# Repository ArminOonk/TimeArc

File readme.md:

# Preparing the raspberry pi

## Update and install packages
Use the following commands to get the RPi ready

	sudo apt-get remove --purge desktop-base lightdm lxappearance lxde-common lxde-icon-theme lxinput lxpanel lxpolkit lxrandr lxsession-edit lxshortcut lxtask lxterminal
	sudo apt-get remove --purge obconf openbox raspberrypi-artwork 
	sudo apt-get remove --purge xarchiver xinit xserver-xorg 
	sudo apt-get remove --purge xserver-xorg-video-fbdev x11-utils x11-common x11-session utils
	sudo apt-get remove wolfram-*
	sudo apt-get update
	sudo apt-get upgrade
	sudo apt-get autoremove
	sudo rpi-update

# ESP Wifi
To get the esp wifi working first check the hardware. The APR2016 version has an error in the schematic. CH_PD is not connected to the correct pin.

In stall the driver using the instruction on the following website: http://oshlab.com/esp8266-raspberry-pi-gpio-wifi/

	cd ~
	git clone https://github.com/oshlab/esp8089.git
	cd esp8089
	sudo sh install
	sudo reboot
	sudo iwlist scan
	ifconfig

Check if wlan0 is visible. Now connect it to the wifi
	
	sudo nano /etc/wpa_supplicant/wpa_supplicant.conf

	network={
	ssid="testing"
	psk="testingPassword"
	}
	
Run the following commands if there is no internet connection (Test by using `ping 8.8.8.8`)

	sudo ifdown wlan0
	sudo ifup wlan0

# Install instructions

## Python packages
install pyfeed-0.7.4 and xe-0.7.4 from the Software directory

## Settings
Create a timearcPrivate.py file using the example

Add the following lines to /etc/rc.local

	sleep 30
	/home/pi/timearc/Software/startup

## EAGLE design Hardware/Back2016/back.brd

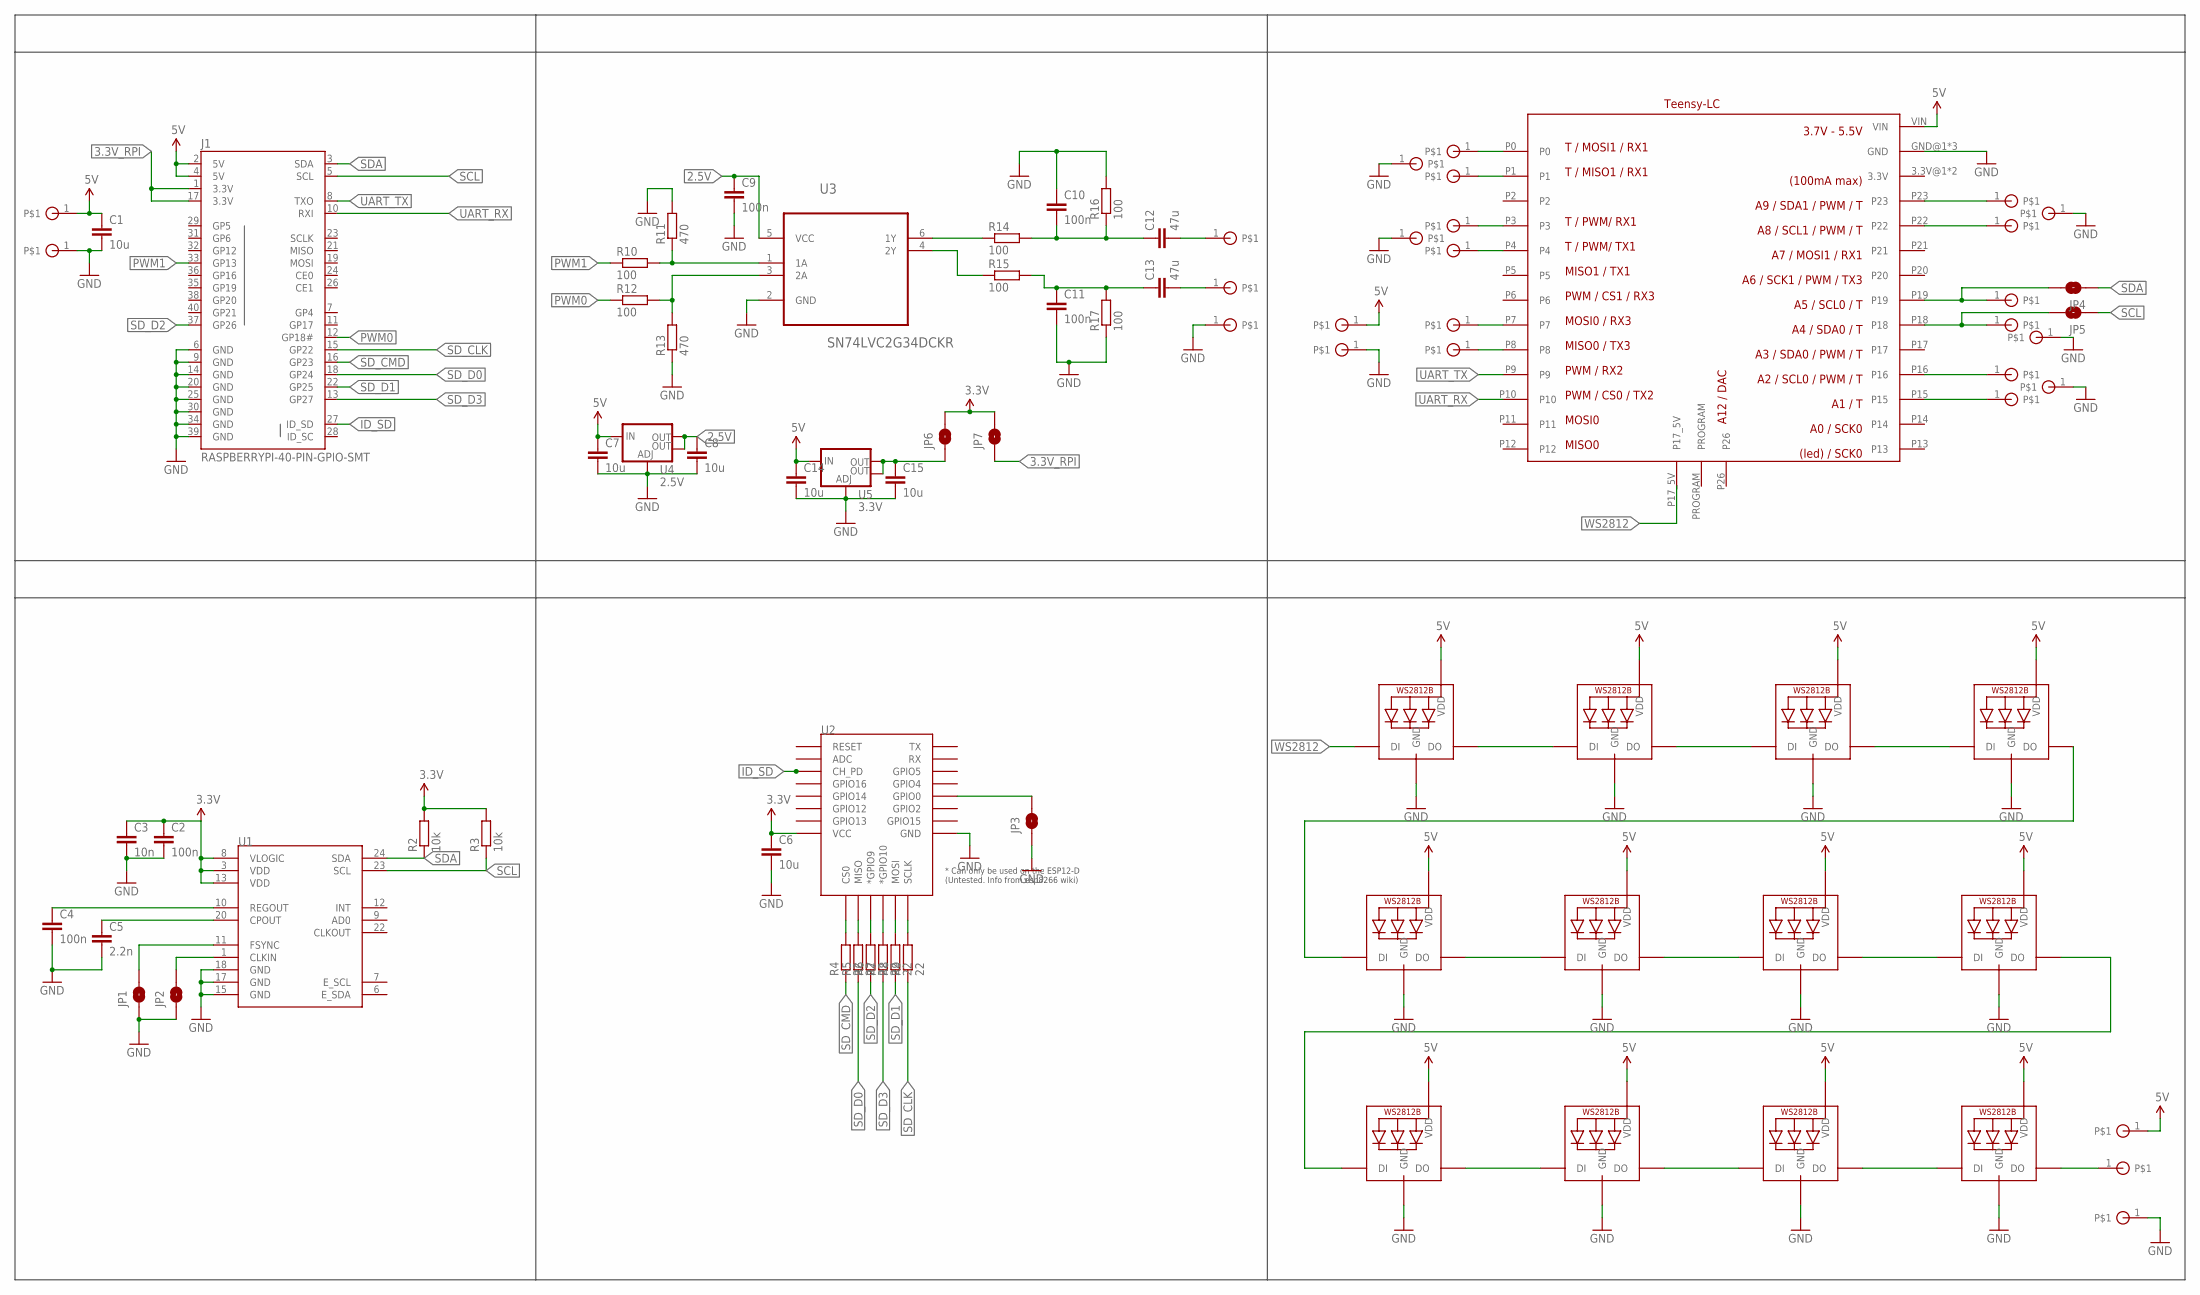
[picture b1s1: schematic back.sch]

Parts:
5V_FRONT, 5V_POWER, 5V_WS1282: SOLDER_PAD
AUDIO_GND: SOLDER_PAD
AUDIO_L: SOLDER_PAD
AUDIO_R: SOLDER_PAD
C1, C6, C7, C8, C14, C15: 10u; C0805
C2, C4, C9, C10, C11: 100n; C0603
C3: 10n; C0603
C5: 2.2n; C0603
C12, C13: 47u; C0805
DO_WS1282: SOLDER_PAD
GND_FRONT: SOLDER_PAD
GND_POWER: SOLDER_PAD
GND_T1_T2, GND_T3_T4, GND_T5_T6, GND_T7_T8: SOLDER_PAD
GND_T_SPARE: SOLDER_PAD
GND_WS2812: SOLDER_PAD
J1: RASPBERRYPI-40-PIN-GPIO-SMT; 2X20-SHROUDED-SMT
JP1, JP2, JP3, JP4, JP5, JP6, JP7: JUMPER-PAD-2-NOYES_SILK; PAD-JUMPER-2-NO_YES_SILK
LED1, LED2, LED3, LED4, LED5, LED6, LED7, LED8, LED9, LED10, LED11, LED12: WS2812B5050; WS2812B
R2, R3: 10k; R0603
R4, R5, R6, R7, R8, R9: 22; R0603
R10, R12, R14, R15, R16, R17: 100; R0603
R11, R13: 470; R0603
RX3: SOLDER_PAD
SCL/TOUCH: SOLDER_PAD
SDA/TOUCH: SOLDER_PAD
TOUCH1, TOUCH2, TOUCH3, TOUCH4, TOUCH5, TOUCH6, TOUCH7, TOUCH8: SOLDER_PAD
TX3: SOLDER_PAD
U1: MPU-9150QFN-24-NP; QFN-24-NP
U2: ESP12ESMD; ESP12E-SMD
U3: SN74LVC2G34DCKR; SOT65P210X110-6N
U4: 2.5V; SOT223
U5: 3.3V; SOT223
U$4: TEENSY_LCSMD; TEENSY_LC_SMD

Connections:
2.5V: C8.1, C9.1, U3.5 (VCC), U4.2 (OUT), U4.4 (OUT)
3.3V: C2.1, C3.1, C6.1, JP6.2, JP7.2, R2.2, R3.2, U1.3 (VDD), U1.8 (VLOGIC), U1.13 (VDD), U2.VCC
3.3V_RPI: J1.1 (3.3V), J1.17 (3.3V), JP7.1
5V: 5V_FRONT.1, 5V_POWER.1, 5V_WS1282.1, C1.1, C7.1, C14.1, J1.2 (5V), J1.4 (5V), LED1.1-VDD (VDD), LED2.1-VDD (VDD), LED3.1-VDD (VDD), LED4.1-VDD (VDD), LED5.1-VDD (VDD), LED6.1-VDD (VDD), LED7.1-VDD (VDD), LED8.1-VDD (VDD), LED9.1-VDD (VDD), LED10.1-VDD (VDD), LED11.1-VDD (VDD), LED12.1-VDD (VDD), U4.3 (IN), U5.3 (IN), U$4.VIN
GND: AUDIO_GND.1, C1.2, C2.2, C3.2, C4.2, C5.2, C6.2, C7.2, C8.2, C9.2, C10.1, C11.2, C14.2, C15.2, GND_FRONT.1, GND_POWER.1, GND_T1_T2.1, GND_T3_T4.1, GND_T5_T6.1, GND_T7_T8.1, GND_T_SPARE.1, GND_WS2812.1, J1.6 (GND), J1.9 (GND), J1.14 (GND), J1.20 (GND), J1.25 (GND), J1.30 (GND), J1.34 (GND), J1.39 (GND), JP1.1, JP2.1, JP3.1, LED1.3-GND (GND), LED2.3-GND (GND), LED3.3-GND (GND), LED4.3-GND (GND), LED5.3-GND (GND), LED6.3-GND (GND), LED7.3-GND (GND), LED8.3-GND (GND), LED9.3-GND (GND), LED10.3-GND (GND), LED11.3-GND (GND), LED12.3-GND (GND), R11.2, R13.1, R16.2, R17.1, U1.15 (GND), U1.17 (GND), U1.18 (GND), U2.GND, U3.2 (GND), U4.1 (ADJ), U5.1 (ADJ), U$4.GND@1 (GND), U$4.GND@2 (GND), U$4.GND@3 (GND)
ID_SD: J1.27 (ID_SD), U2.CH_PD
unnamed: JP2.2, U1.1 (CLKIN)
unnamed: JP1.2, U1.11 (FSYNC)
unnamed: C5.1, U1.20 (CPOUT)
unnamed: C4.1, U1.10 (REGOUT)
unnamed: R14.1, U3.6 (1Y)
unnamed: R4.2, U2.CS0
unnamed: R5.2, U2.MISO
unnamed: R6.2, U2.GPIO9 (*GPIO9)
unnamed: R7.2, U2.GPIO10 (*GPIO10)
unnamed: R8.2, U2.MOSI
unnamed: R9.2, U2.SCLK
unnamed: JP3.2, U2.GPIO0
unnamed: R10.2, R11.1, U3.1 (1A)
unnamed: R12.2, R13.2, U3.3 (2A)
unnamed: R15.1, U3.4 (2Y)
unnamed: C10.2, C12.1, R14.2, R16.1
unnamed: C11.1, C13.1, R15.2, R17.2
unnamed: LED1.2-DOUT (DO), LED2.4-DIN (DI)
unnamed: AUDIO_L.1, C12.2
unnamed: AUDIO_R.1, C13.2
unnamed: TOUCH1.1, U$4.P0
unnamed: TOUCH2.1, U$4.P1
unnamed: TOUCH3.1, U$4.P3
unnamed: TOUCH4.1, U$4.P4
unnamed: TOUCH5.1, U$4.P23
unnamed: TOUCH6.1, U$4.P22
unnamed: JP4.2, SDA/TOUCH.1, U$4.P19
unnamed: JP5.2, SCL/TOUCH.1, U$4.P18
unnamed: TOUCH7.1, U$4.P16
unnamed: TOUCH8.1, U$4.P15
unnamed: RX3.1, U$4.P7
unnamed: TX3.1, U$4.P8
unnamed: LED2.2-DOUT (DO), LED3.4-DIN (DI)
unnamed: LED3.2-DOUT (DO), LED4.4-DIN (DI)
unnamed: LED4.2-DOUT (DO), LED5.4-DIN (DI)
unnamed: LED5.2-DOUT (DO), LED6.4-DIN (DI)
unnamed: LED6.2-DOUT (DO), LED7.4-DIN (DI)
unnamed: LED7.2-DOUT (DO), LED8.4-DIN (DI)
unnamed: LED8.2-DOUT (DO), LED9.4-DIN (DI)
unnamed: LED9.2-DOUT (DO), LED10.4-DIN (DI)
unnamed: LED10.2-DOUT (DO), LED11.4-DIN (DI)
unnamed: LED11.2-DOUT (DO), LED12.4-DIN (DI)
unnamed: DO_WS1282.1, LED12.2-DOUT (DO)
unnamed: C15.1, JP6.1, U5.2 (OUT), U5.4 (OUT)
PWM0: J1.12 (GP18#), R12.1
PWM1: J1.33 (GP13), R10.1
SCL: J1.5 (SCL), JP5.1, R3.1, U1.23 (SCL)
SDA: J1.3 (SDA), JP4.1, R2.1, U1.24 (SDA)
SD_CLK: J1.15 (GP22), R9.1
SD_CMD: J1.16 (GP23), R4.1
SD_D0: J1.18 (GP24), R5.1
SD_D1: J1.22 (GP25), R8.1
SD_D2: J1.37 (GP26), R6.1
SD_D3: J1.13 (GP27), R7.1
UART_RX: J1.10 (RXI), U$4.P10
UART_TX: J1.8 (TXO), U$4.P9
WS2812: LED1.4-DIN (DI), U$4.P17_5V

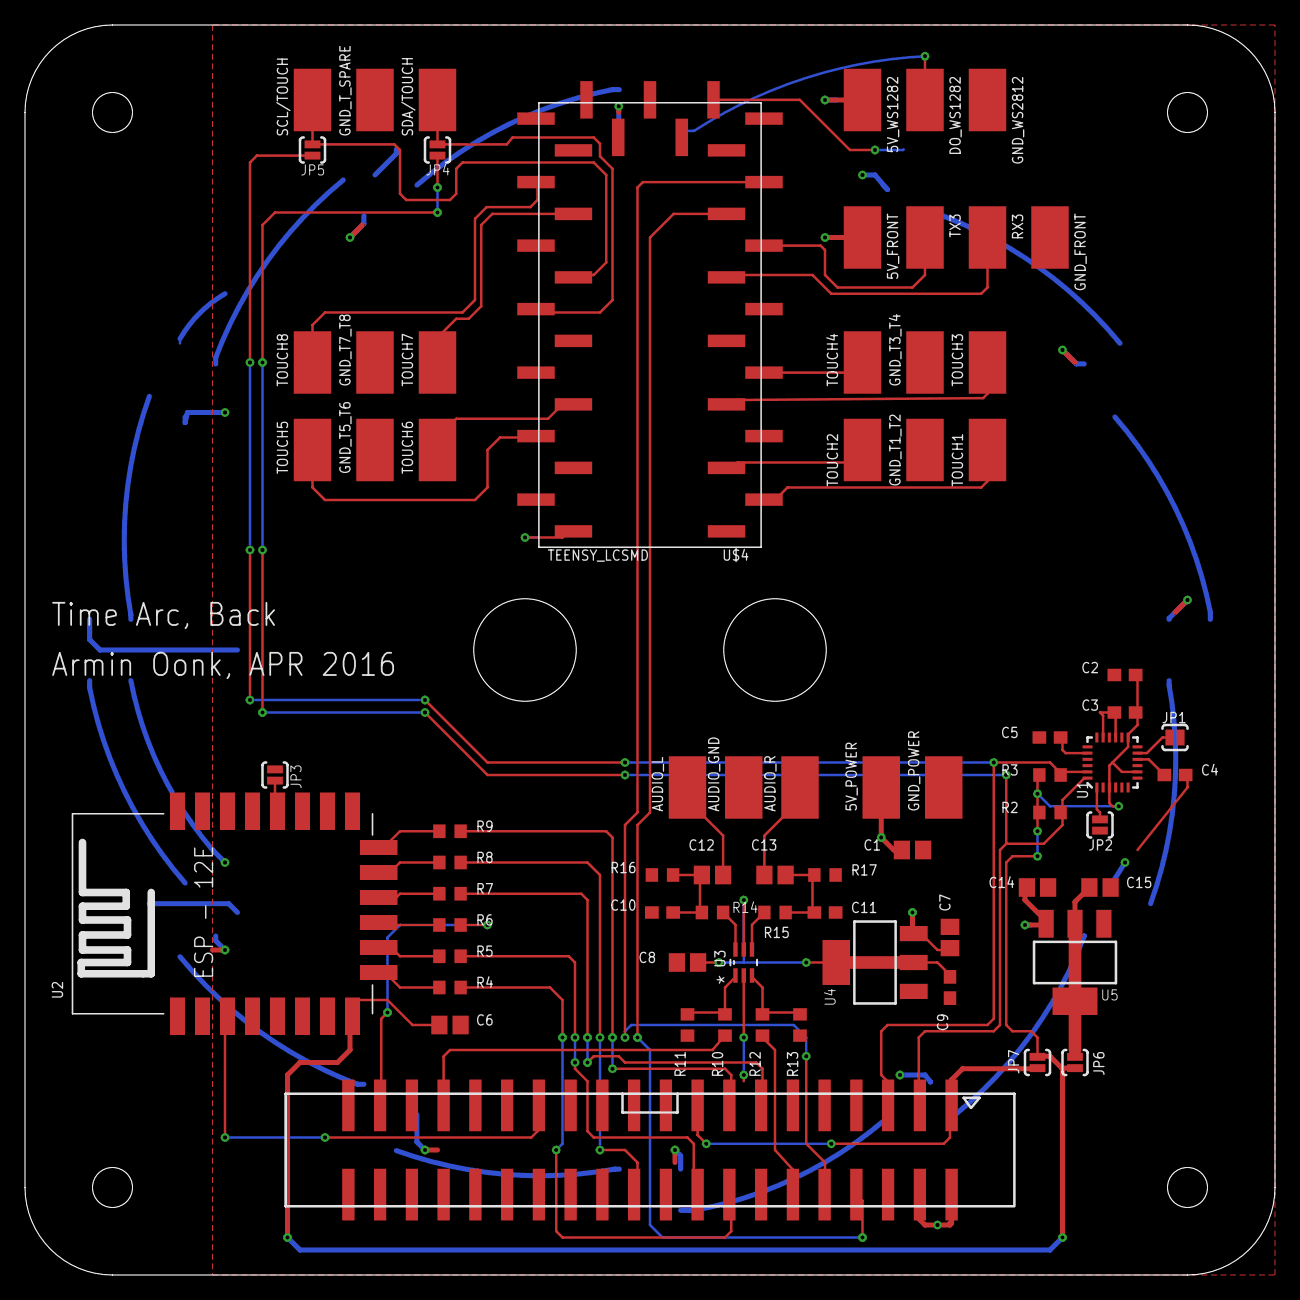
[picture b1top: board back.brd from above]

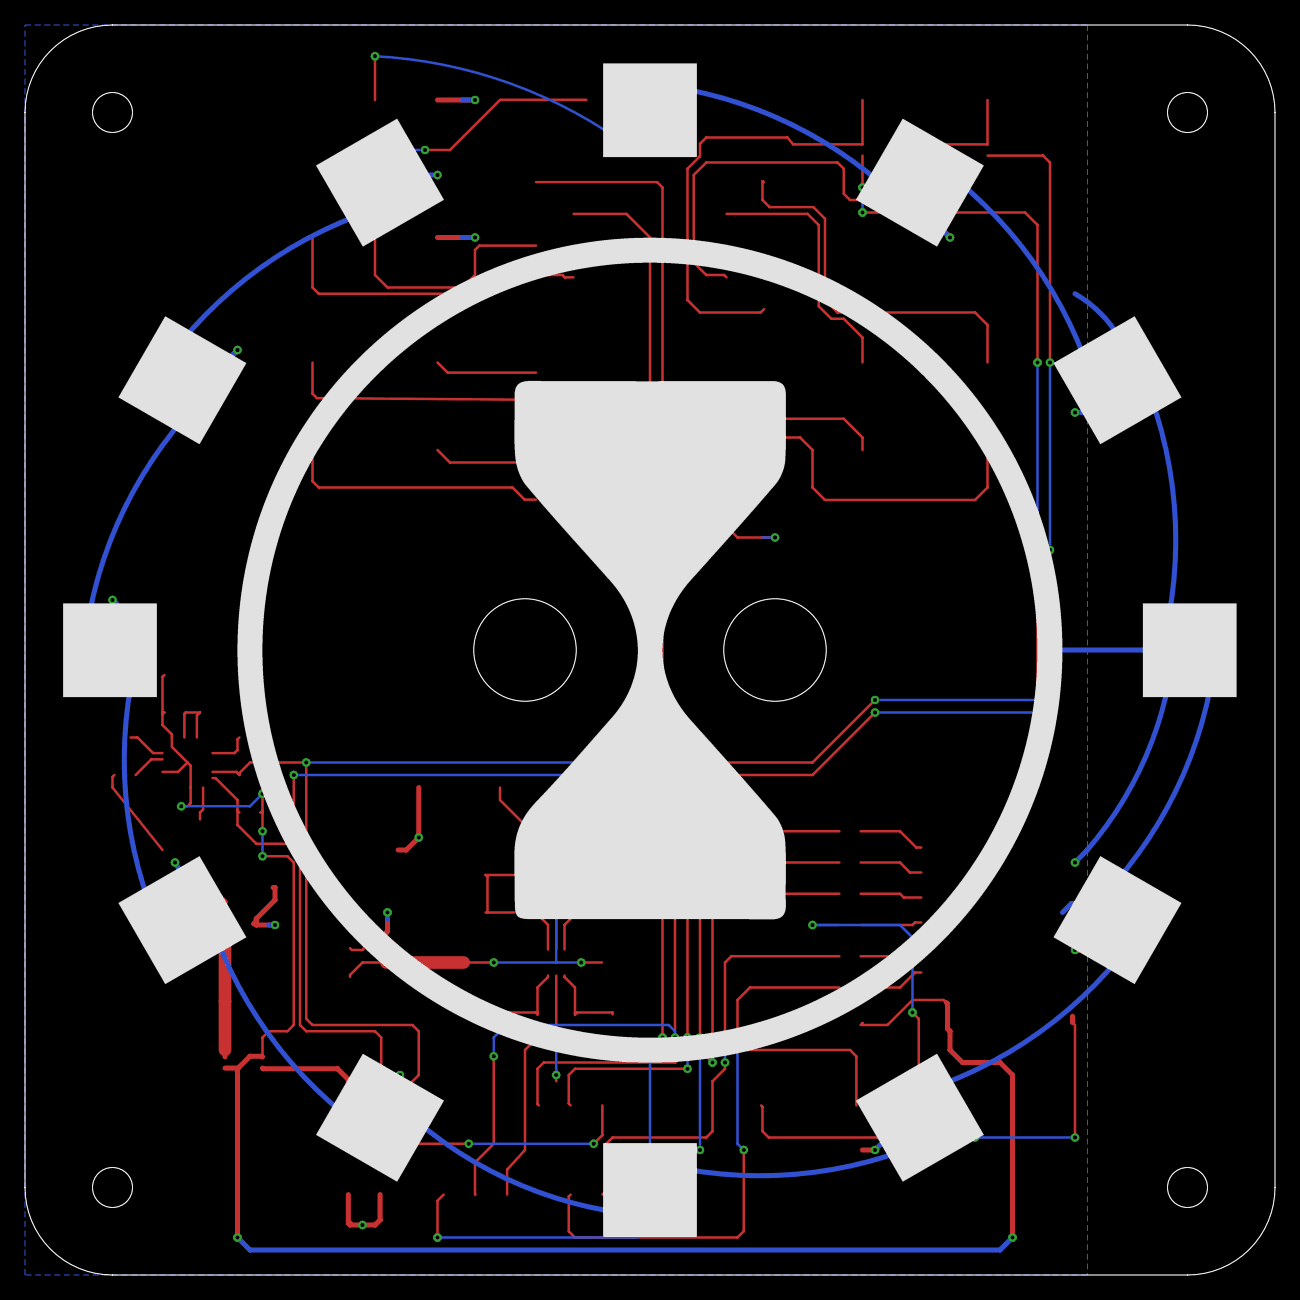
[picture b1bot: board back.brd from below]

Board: 2 copper layers, 100.0 x 100.0 mm, 86 parts (13 on the bottom side), 63 nets.

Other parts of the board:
U$1: TIMEARC_LOGO
U$15: TIMEARC_KEEPOUT

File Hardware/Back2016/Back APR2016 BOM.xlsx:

| Part | Value | Device | Description | Manufacturer | MPN | OC_FARNELL | Link
 | C1 | 10u | C-EUC0805 | CAPACITOR, European symbol |  |  | 2320856
 | C2 | 100n | C-EUC0603 | CAPACITOR, European symbol |  |  | 2496832
 | C3 | 10n | C-EUC0603 | CAPACITOR, European symbol |  |  | 2496826
 | C4 | 100n | C-EUC0603 | CAPACITOR, European symbol |  |  | 2496832
 | C5 | 2.2n | C-EUC0603 | CAPACITOR, European symbol |  |  | 2496845
 | C6 | 10u | C-EUC0805 | CAPACITOR, European symbol |  |  | 2320856
 | C7 | 10u | C-EUC0805 | CAPACITOR, European symbol |  |  | 2320856
 | C8 | 10u | C-EUC0805 | CAPACITOR, European symbol |  |  | 2320856
 | C9 | 100n | C-EUC0603 | CAPACITOR, European symbol |  |  | 2496832
 | C10 | 100n | C-EUC0603 | CAPACITOR, European symbol |  |  | 2496832
 | C11 | 100n | C-EUC0603 | CAPACITOR, European symbol |  |  | 2496832
 | C12 | 47u | C-EUC0805 | CAPACITOR, European symbol |  |  | 2362109
 | C13 | 47u | C-EUC0805 | CAPACITOR, European symbol |  |  | 2362109
 | C14 | 10u | C-EUC0805 | CAPACITOR, European symbol |  |  | 2320856
 | C15 | 10u | C-EUC0805 | CAPACITOR, European symbol |  |  | 2320856
 | J1 | RASPBERRYPI-40-PIN-GPIO-SMT | RASPBERRYPI-40-PIN-GPIO-SMT | Second Generation Raspberry Pi GPIO Header |  |  | 1256663
 | LED1 | WS2812B5050 | WS2812B5050 |  |  |  |  | http://www.aliexpress.com/item/10-1000pcs-WS2812B-4pins-5050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
 | LED2 | WS2812B5050 | WS2812B5050 |  |  |  |  | http://www.aliexpress.com/item/10-1000pcs-WS2812B-4pins-5050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
 | LED3 | WS2812B5050 | WS2812B5050 |  |  |  |  | http://www.aliexpress.com/item/10-1000pcs-WS2812B-4pins-5050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
 | LED4 | WS2812B5050 | WS2812B5050 |  |  |  |  | http://www.aliexpress.com/item/10-1000pcs-WS2812B-4pins-5050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
 | LED5 | WS2812B5050 | WS2812B5050 |  |  |  |  | http://www.aliexpress.com/item/10-1000pcs-WS2812B-4pins-5050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
 | LED6 | WS2812B5050 | WS2812B5050 |  |  |  |  | http://www.aliexpress.com/item/10-1000pcs-WS2812B-4pins-5050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
 | LED7 | WS2812B5050 | WS2812B5050 |  |  |  |  | http://www.aliexpress.com/item/10-1000pcs-WS2812B-4pins-5050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
 | LED8 | WS2812B5050 | WS2812B5050 |  |  |  |  | http://www.aliexpress.com/item/10-1000pcs-WS2812B-4pins-5050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
 | LED9 | WS2812B5050 | WS2812B5050 |  |  |  |  | http://www.aliexpress.com/item/10-1000pcs-WS2812B-4pins-5050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
 | LED10 | WS2812B5050 | WS2812B5050 |  |  |  |  | http://www.aliexpress.com/item/10-1000pcs-WS2812B-4pins-5050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
 | LED11 | WS2812B5050 | WS2812B5050 |  |  |  |  | http://www.aliexpress.com/item/10-1000pcs-WS2812B-4pins-5050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
 | LED12 | WS2812B5050 | WS2812B5050 |  |  |  |  | http://www.aliexpress.com/item/10-1000pcs-WS2812B-4pins-5050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
 | R2 | 10k | R-EU_R0603 | RESISTOR, European symbol |  |  | 1469748
 | R3 | 10k | R-EU_R0603 | RESISTOR, European symbol |  |  | 1469748
 | R4 | 22 | R-EU_R0603 | RESISTOR, European symbol |  |  | 9330844
 | R5 | 22 | R-EU_R0603 | RESISTOR, European symbol |  |  | 9330844
 | R6 | 22 | R-EU_R0603 | RESISTOR, European symbol |  |  | 9330844
 | R7 | 22 | R-EU_R0603 | RESISTOR, European symbol |  |  | 9330844
 | R8 | 22 | R-EU_R0603 | RESISTOR, European symbol |  |  | 9330844
 | R9 | 22 | R-EU_R0603 | RESISTOR, European symbol |  |  | 9330844
 | R10 | 100 | R-EU_R0603 | RESISTOR, European symbol |  |  | 2130776
 | R11 | 470 | R-EU_R0603 | RESISTOR, European symbol |  |  | 2447374
 | R12 | 100 | R-EU_R0603 | RESISTOR, European symbol |  |  | 2130776
 | R13 | 470 | R-EU_R0603 | RESISTOR, European symbol |  |  | 2447374
 | R14 | 100 | R-EU_R0603 | RESISTOR, European symbol |  |  | 2130776
 | R15 | 100 | R-EU_R0603 | RESISTOR, European symbol |  |  | 2130776
 | R16 | 100 | R-EU_R0603 | RESISTOR, European symbol |  |  | 2130776
 | R17 | 100 | R-EU_R0603 | RESISTOR, European symbol |  |  | 2130776
 | U$4 | TEENSY_LCSMD | TEENSY_LCSMD | Teensy LC |  |  | 2356213
 | U1 |  | MPU-9150QFN-24-NP | 9DOF (3mag, 3accel, 3rotat). I2C interface. |  |  |  | http://www.aliexpress.com/item/Free-shipping-1pcs-lot-MPU-91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
 | U2 |  | ESP12ESMD | ESP12E Module |  |  |  | http://www.aliexpress.com/item/2015-New-version-1PCS-ESP-12F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
 | U3 | SN74LVC2G34DCKR | SN74LVC2G34DCKR | DUAL BUFFER GATE |  | SN74LVC2G34DCKR | 1595409
 | U4 | 2.5V | V_REG_LM1117SOT223 | Voltage Regulator LM1117 |  |  | 1564629
 | U5 | 3.3V | V_REG_LM1117SOT223 | Voltage Regulator LM1117 |  |  | 1469051
 |  |  |  | Power jack panel mount |  |  | 1216726
 |  |  |  | Jack 3.5 mm panel mount |  |  | 1267396
 | Solder PADS
 | 5V_FRONT | SOLDER_PAD | SOLDER_PAD
 | 5V_POWER | SOLDER_PAD | SOLDER_PAD
 | 5V_WS1282 | SOLDER_PAD | SOLDER_PAD
 | AUDIO_GND | SOLDER_PAD | SOLDER_PAD
 | AUDIO_L | SOLDER_PAD | SOLDER_PAD
 | AUDIO_R | SOLDER_PAD | SOLDER_PAD
 | DO_WS1282 | SOLDER_PAD | SOLDER_PAD
 | GND_FRONT | SOLDER_PAD | SOLDER_PAD
 | GND_POWER | SOLDER_PAD | SOLDER_PAD
 | GND_T1_T2 | SOLDER_PAD | SOLDER_PAD
 | GND_T3_T4 | SOLDER_PAD | SOLDER_PAD
 | GND_T5_T6 | SOLDER_PAD | SOLDER_PAD
 | GND_T7_T8 | SOLDER_PAD | SOLDER_PAD
 | GND_T_SPARE | SOLDER_PAD | SOLDER_PAD
 | GND_WS2812 | SOLDER_PAD | SOLDER_PAD
 | RX3 | SOLDER_PAD | SOLDER_PAD
 | SCL/TOUCH | SOLDER_PAD | SOLDER_PAD
 | SDA/TOUCH | SOLDER_PAD | SOLDER_PAD
 | TOUCH1 | SOLDER_PAD | SOLDER_PAD
 | TOUCH2 | SOLDER_PAD | SOLDER_PAD
 | TOUCH3 | SOLDER_PAD | SOLDER_PAD
 | TOUCH4 | SOLDER_PAD | SOLDER_PAD
 | TOUCH5 | SOLDER_PAD | SOLDER_PAD
 | TOUCH6 | SOLDER_PAD | SOLDER_PAD
 | TOUCH7 | SOLDER_PAD | SOLDER_PAD
 | TOUCH8 | SOLDER_PAD | SOLDER_PAD
 | TX3 | SOLDER_PAD | SOLDER_PAD
 | Jumpers
 | JP1 | JUMPER-PAD-2-NOYES_SILK | JUMPER-PAD-2-NOYES_SILK
 | JP2 | JUMPER-PAD-2-NOYES_SILK | JUMPER-PAD-2-NOYES_SILK
 | JP3 | JUMPER-PAD-2-NOYES_SILK | JUMPER-PAD-2-NOYES_SILK
 | JP4 | JUMPER-PAD-2-NOYES_SILK | JUMPER-PAD-2-NOYES_SILK
 | JP5 | JUMPER-PAD-2-NOYES_SILK | JUMPER-PAD-2-NOYES_SILK
 | JP6 | JUMPER-PAD-2-NOYES_SILK | JUMPER-PAD-2-NOYES_SILK
 | JP7 | JUMPER-PAD-2-NOYES_SILK | JUMPER-PAD-2-NOYES_SILK

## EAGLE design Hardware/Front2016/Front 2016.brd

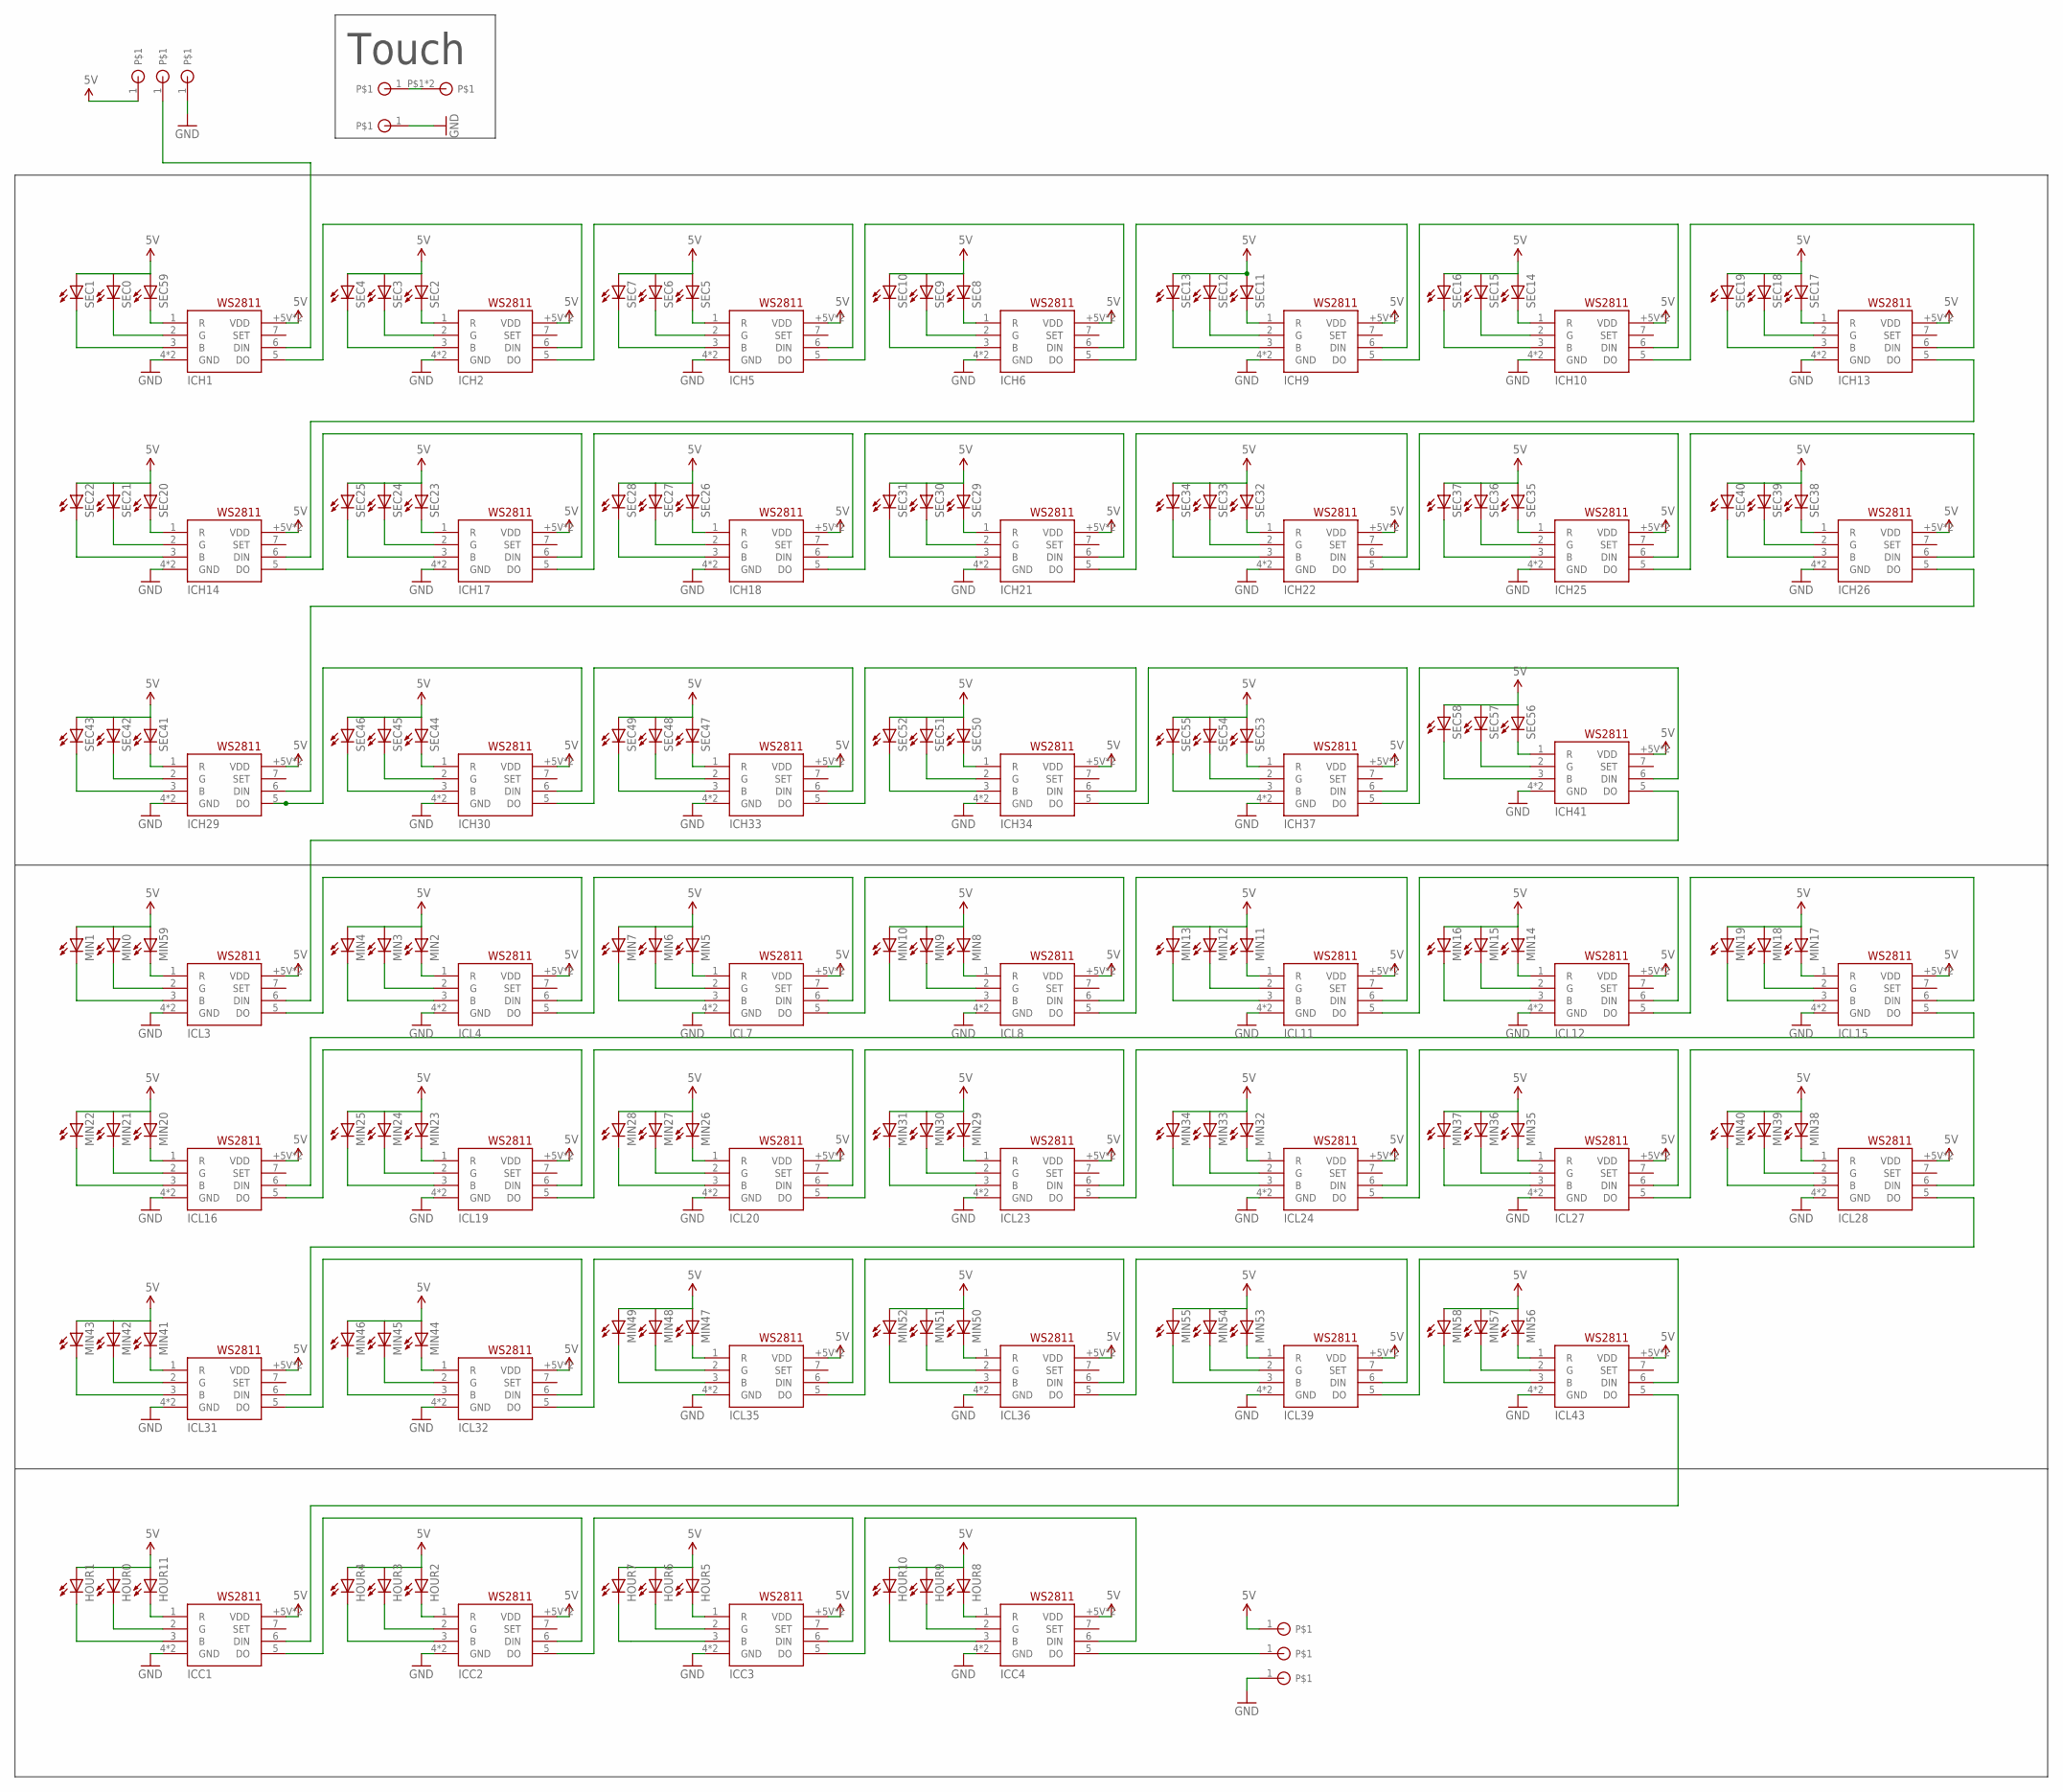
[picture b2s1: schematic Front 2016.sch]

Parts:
+5V, +5V1: SOLDER_PAD
DIN: SOLDER_PAD
DOUT: SOLDER_PAD
GND, GND46, GND48: SOLDER_PAD
HOUR0, HOUR1, HOUR2, HOUR3, HOUR4, HOUR5, HOUR6, HOUR7, HOUR8, HOUR9, HOUR10, HOUR11: LEDCHIPLED_0603; CHIPLED_0603
ICC1, ICC2, ICC3, ICC4: WS2811-SOP8; SO08-SKINNYPADS
ICH1, ICH2, ICH5, ICH6, ICH9, ICH10, ICH13, ICH14, ICH17, ICH18, ICH21, ICH22, ICH25, ICH26, ICH29, ICH30, ICH33, ICH34, ICH37, ICH41: WS2811-SOP8; SO08-SKINNYPADS
ICL3, ICL4, ICL7, ICL8, ICL11, ICL12, ICL15, ICL16, ICL19, ICL20, ICL23, ICL24, ICL27, ICL28, ICL31, ICL32, ICL35, ICL36, ICL39, ICL43: WS2811-SOP8; SO08-SKINNYPADS
MIN0, MIN1, MIN2, MIN3, MIN4, MIN5, MIN6, MIN7, MIN8, MIN9, MIN10, MIN11, MIN12, MIN13, MIN14, MIN15, MIN16, MIN17, MIN18, MIN19, MIN20, MIN21, MIN22, MIN23, MIN24, MIN25, MIN26, MIN27, MIN28, MIN29, MIN30, MIN31, MIN32, MIN33, MIN34, MIN35, MIN36, MIN37, MIN38, MIN39, MIN40, MIN41, MIN42, MIN43, MIN44, MIN45, MIN46, MIN47, MIN48, MIN49, MIN50, MIN51, MIN52, MIN53, MIN54, MIN55, MIN56, MIN57, MIN58, MIN59: LEDCHIPLED_0603; CHIPLED_0603
SEC0, SEC1, SEC2, SEC3, SEC4, SEC5, SEC6, SEC7, SEC8, SEC9, SEC10, SEC11, SEC12, SEC13, SEC14, SEC15, SEC16, SEC17, SEC18, SEC19, SEC20, SEC21, SEC22, SEC23, SEC24, SEC25, SEC26, SEC27, SEC28, SEC29, SEC30, SEC31, SEC32, SEC33, SEC34, SEC35, SEC36, SEC37, SEC38, SEC39, SEC40, SEC41, SEC42, SEC43, SEC44, SEC45, SEC46, SEC47, SEC48, SEC49, SEC50, SEC51, SEC52, SEC53, SEC54, SEC55, SEC56, SEC57, SEC58, SEC59: LEDCHIPLED_0603; CHIPLED_0603
TOUCH: SOLDER_PAD
U$2: TOUCH_PAD_LARGE

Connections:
5V: +5V.1, +5V1.1, HOUR0.A, HOUR1.A, HOUR2.A, HOUR3.A, HOUR4.A, HOUR5.A, HOUR6.A, HOUR7.A, HOUR8.A, HOUR9.A, HOUR10.A, HOUR11.A, ICC1.8 (VDD), ICC1.+5V (VDD), ICC2.8 (VDD), ICC2.+5V (VDD), ICC3.8 (VDD), ICC3.+5V (VDD), ICC4.8 (VDD), ICC4.+5V (VDD), ICH1.8 (VDD), ICH1.+5V (VDD), ICH2.8 (VDD), ICH2.+5V (VDD), ICH5.8 (VDD), ICH5.+5V (VDD), ICH6.8 (VDD), ICH6.+5V (VDD), ICH9.8 (VDD), ICH9.+5V (VDD), ICH10.8 (VDD), ICH10.+5V (VDD), ICH13.8 (VDD), ICH13.+5V (VDD), ICH14.8 (VDD), ICH14.+5V (VDD), ICH17.8 (VDD), ICH17.+5V (VDD), ICH18.8 (VDD), ICH18.+5V (VDD), ICH21.8 (VDD), ICH21.+5V (VDD), ICH22.8 (VDD), ICH22.+5V (VDD), ICH25.8 (VDD), ICH25.+5V (VDD), ICH26.8 (VDD), ICH26.+5V (VDD), ICH29.8 (VDD), ICH29.+5V (VDD), ICH30.8 (VDD), ICH30.+5V (VDD), ICH33.8 (VDD), ICH33.+5V (VDD), ICH34.8 (VDD), ICH34.+5V (VDD), ICH37.8 (VDD), ICH37.+5V (VDD), ICH41.8 (VDD), ICH41.+5V (VDD), ICL3.8 (VDD), ICL3.+5V (VDD), ICL4.8 (VDD), ICL4.+5V (VDD), ICL7.8 (VDD), ICL7.+5V (VDD), ICL8.8 (VDD), ICL8.+5V (VDD), ICL11.8 (VDD), ICL11.+5V (VDD), ICL12.8 (VDD), ICL12.+5V (VDD), ICL15.8 (VDD), ICL15.+5V (VDD), ICL16.8 (VDD), ICL16.+5V (VDD), ICL19.8 (VDD), ICL19.+5V (VDD), ICL20.8 (VDD), ICL20.+5V (VDD), ICL23.8 (VDD), ICL23.+5V (VDD), ICL24.8 (VDD), ICL24.+5V (VDD), ICL27.8 (VDD), ICL27.+5V (VDD), ICL28.8 (VDD), ICL28.+5V (VDD), ICL31.8 (VDD), ICL31.+5V (VDD), ICL32.8 (VDD), ICL32.+5V (VDD), ICL35.8 (VDD), ICL35.+5V (VDD), ICL36.8 (VDD), ICL36.+5V (VDD), ICL39.8 (VDD), ICL39.+5V (VDD), ICL43.8 (VDD), ICL43.+5V (VDD), MIN0.A, MIN1.A, MIN2.A, MIN3.A, MIN4.A, MIN5.A, MIN6.A, MIN7.A, MIN8.A, MIN9.A, MIN10.A, MIN11.A, MIN12.A, MIN13.A, MIN14.A, MIN15.A, MIN16.A, MIN17.A, MIN18.A, MIN19.A, MIN20.A, MIN21.A, MIN22.A, MIN23.A, MIN24.A, MIN25.A, MIN26.A, MIN27.A, MIN28.A, MIN29.A, MIN30.A, MIN31.A, MIN32.A, MIN33.A, MIN34.A, MIN35.A, MIN36.A, MIN37.A, MIN38.A, MIN39.A, MIN40.A, MIN41.A, MIN42.A, MIN43.A, MIN44.A, MIN45.A, MIN46.A, MIN47.A, MIN48.A, MIN49.A, MIN50.A, MIN51.A, MIN52.A, MIN53.A, MIN54.A, MIN55.A, MIN56.A, MIN57.A, MIN58.A, MIN59.A, SEC0.A, SEC1.A, SEC2.A, SEC3.A, SEC4.A, SEC5.A, SEC6.A, SEC7.A, SEC8.A, SEC9.A, SEC10.A, SEC11.A, SEC12.A, SEC13.A, SEC14.A, SEC15.A, SEC16.A, SEC17.A, SEC18.A, SEC19.A, SEC20.A, SEC21.A, SEC22.A, SEC23.A, SEC24.A, SEC25.A, SEC26.A, SEC27.A, SEC28.A, SEC29.A, SEC30.A, SEC31.A, SEC32.A, SEC33.A, SEC34.A, SEC35.A, SEC36.A, SEC37.A, SEC38.A, SEC39.A, SEC40.A, SEC41.A, SEC42.A, SEC43.A, SEC44.A, SEC45.A, SEC46.A, SEC47.A, SEC48.A, SEC49.A, SEC50.A, SEC51.A, SEC52.A, SEC53.A, SEC54.A, SEC55.A, SEC56.A, SEC57.A, SEC58.A, SEC59.A
GND: GND.1, GND46.1, GND48.1, ICC1.4 (GND), ICC1.GND, ICC2.4 (GND), ICC2.GND, ICC3.4 (GND), ICC3.GND, ICC4.4 (GND), ICC4.GND, ICH1.4 (GND), ICH1.GND, ICH2.4 (GND), ICH2.GND, ICH5.4 (GND), ICH5.GND, ICH6.4 (GND), ICH6.GND, ICH9.4 (GND), ICH9.GND, ICH10.4 (GND), ICH10.GND, ICH13.4 (GND), ICH13.GND, ICH14.4 (GND), ICH14.GND, ICH17.4 (GND), ICH17.GND, ICH18.4 (GND), ICH18.GND, ICH21.4 (GND), ICH21.GND, ICH22.4 (GND), ICH22.GND, ICH25.4 (GND), ICH25.GND, ICH26.4 (GND), ICH26.GND, ICH29.4 (GND), ICH29.GND, ICH30.4 (GND), ICH30.GND, ICH33.4 (GND), ICH33.GND, ICH34.4 (GND), ICH34.GND, ICH37.4 (GND), ICH37.GND, ICH41.4 (GND), ICH41.GND, ICL3.4 (GND), ICL3.GND, ICL4.4 (GND), ICL4.GND, ICL7.4 (GND), ICL7.GND, ICL8.4 (GND), ICL8.GND, ICL11.4 (GND), ICL11.GND, ICL12.4 (GND), ICL12.GND, ICL15.4 (GND), ICL15.GND, ICL16.4 (GND), ICL16.GND, ICL19.4 (GND), ICL19.GND, ICL20.4 (GND), ICL20.GND, ICL23.4 (GND), ICL23.GND, ICL24.4 (GND), ICL24.GND, ICL27.4 (GND), ICL27.GND, ICL28.4 (GND), ICL28.GND, ICL31.4 (GND), ICL31.GND, ICL32.4 (GND), ICL32.GND, ICL35.4 (GND), ICL35.GND, ICL36.4 (GND), ICL36.GND, ICL39.4 (GND), ICL39.GND, ICL43.4 (GND), ICL43.GND
unnamed: ICH1.1 (R), SEC59.C
unnamed: ICH1.3 (B), SEC1.C
unnamed: ICH1.2 (G), SEC0.C
unnamed: ICH2.1 (R), SEC2.C
unnamed: ICH2.2 (G), SEC3.C
unnamed: ICH2.3 (B), SEC4.C
unnamed: ICH5.1 (R), SEC5.C
unnamed: ICH5.2 (G), SEC6.C
unnamed: ICH5.3 (B), SEC7.C
unnamed: ICH6.1 (R), SEC8.C
unnamed: ICH6.2 (G), SEC9.C
unnamed: ICH6.3 (B), SEC10.C
unnamed: ICH13.1 (R), SEC17.C
unnamed: ICH9.1 (R), SEC11.C
unnamed: ICH9.2 (G), SEC12.C
unnamed: ICH9.3 (B), SEC13.C
unnamed: ICH26.2 (G), SEC39.C
unnamed: ICH10.1 (R), SEC14.C
unnamed: ICH10.2 (G), SEC15.C
unnamed: ICH10.3 (B), SEC16.C
unnamed: ICH14.1 (R), SEC20.C
unnamed: ICH13.2 (G), SEC18.C
unnamed: ICH13.3 (B), SEC19.C
unnamed: ICH14.2 (G), SEC21.C
unnamed: ICH14.3 (B), SEC22.C
unnamed: ICH26.3 (B), SEC40.C
unnamed: ICH17.1 (R), SEC23.C
unnamed: ICH17.2 (G), SEC24.C
unnamed: ICH17.3 (B), SEC25.C
unnamed: ICH18.1 (R), SEC26.C
unnamed: ICH18.2 (G), SEC27.C
unnamed: ICH18.3 (B), SEC28.C
unnamed: ICH29.5 (DO), ICH30.6 (DIN)
unnamed: ICH29.1 (R), SEC41.C
unnamed: ICH21.1 (R), SEC29.C
unnamed: ICH21.2 (G), SEC30.C
unnamed: ICH21.3 (B), SEC31.C
unnamed: ICH29.2 (G), SEC42.C
unnamed: ICH22.1 (R), SEC32.C
unnamed: ICH22.2 (G), SEC33.C
unnamed: ICH22.3 (B), SEC34.C
unnamed: ICH29.3 (B), SEC43.C
unnamed: ICH25.1 (R), SEC35.C
unnamed: ICH25.2 (G), SEC36.C
unnamed: ICH25.3 (B), SEC37.C
unnamed: ICH30.5 (DO), ICH33.6 (DIN)
unnamed: ICH26.1 (R), SEC38.C
unnamed: ICH30.1 (R), SEC44.C
unnamed: ICH30.2 (G), SEC45.C
unnamed: ICH30.3 (B), SEC46.C
unnamed: ICH33.5 (DO), ICH34.6 (DIN)
unnamed: ICH33.1 (R), SEC47.C
unnamed: ICH33.2 (G), SEC48.C
unnamed: ICH33.3 (B), SEC49.C
unnamed: ICH34.5 (DO), ICH37.6 (DIN)
unnamed: ICH34.1 (R), SEC50.C
unnamed: ICH34.2 (G), SEC51.C
unnamed: ICH34.3 (B), SEC52.C
unnamed: ICH37.5 (DO), ICH41.6 (DIN)
unnamed: ICH37.1 (R), SEC53.C
unnamed: ICH37.2 (G), SEC54.C
unnamed: ICH37.3 (B), SEC55.C
unnamed: ICH41.5 (DO), ICL3.6 (DIN)
unnamed: ICH41.1 (R), SEC56.C
unnamed: ICH41.2 (G), SEC57.C
unnamed: ICH41.3 (B), SEC58.C
unnamed: ICH1.5 (DO), ICH2.6 (DIN)
unnamed: ICH2.5 (DO), ICH5.6 (DIN)
unnamed: ICH5.5 (DO), ICH6.6 (DIN)
unnamed: ICH6.5 (DO), ICH9.6 (DIN)
unnamed: ICH9.5 (DO), ICH10.6 (DIN)
unnamed: ICH10.5 (DO), ICH13.6 (DIN)
unnamed: ICH13.5 (DO), ICH14.6 (DIN)
unnamed: ICH14.5 (DO), ICH17.6 (DIN)
unnamed: ICH17.5 (DO), ICH18.6 (DIN)
unnamed: ICH18.5 (DO), ICH21.6 (DIN)
unnamed: ICH21.5 (DO), ICH22.6 (DIN)
unnamed: ICH22.5 (DO), ICH25.6 (DIN)
unnamed: ICH25.5 (DO), ICH26.6 (DIN)
unnamed: ICH26.5 (DO), ICH29.6 (DIN)
unnamed: ICL3.1 (R), MIN59.C
unnamed: ICL3.2 (G), MIN0.C
unnamed: ICL3.3 (B), MIN1.C
unnamed: ICL4.1 (R), MIN2.C
unnamed: ICL4.2 (G), MIN3.C
unnamed: ICL4.3 (B), MIN4.C
unnamed: ICL7.1 (R), MIN5.C
unnamed: ICL7.2 (G), MIN6.C
unnamed: ICL7.3 (B), MIN7.C
unnamed: ICL8.1 (R), MIN8.C
unnamed: ICL8.2 (G), MIN9.C
unnamed: ICL8.3 (B), MIN10.C
unnamed: ICL3.5 (DO), ICL4.6 (DIN)
unnamed: ICL4.5 (DO), ICL7.6 (DIN)
unnamed: ICL11.1 (R), MIN11.C
unnamed: ICL11.2 (G), MIN12.C
unnamed: ICL11.3 (B), MIN13.C
unnamed: ICL7.5 (DO), ICL8.6 (DIN)
unnamed: ICL12.1 (R), MIN14.C
unnamed: ICL12.2 (G), MIN15.C
unnamed: ICL12.3 (B), MIN16.C
unnamed: ICL8.5 (DO), ICL11.6 (DIN)
unnamed: ICL15.1 (R), MIN17.C
unnamed: ICL15.2 (G), MIN18.C
unnamed: ICL15.3 (B), MIN19.C
unnamed: ICL11.5 (DO), ICL12.6 (DIN)
unnamed: ICL16.1 (R), MIN20.C
unnamed: ICL16.2 (G), MIN21.C
unnamed: ICL16.3 (B), MIN22.C
unnamed: ICL12.5 (DO), ICL15.6 (DIN)
unnamed: ICL19.1 (R), MIN23.C
unnamed: ICL19.2 (G), MIN24.C
unnamed: ICL19.3 (B), MIN25.C
unnamed: ICL15.5 (DO), ICL16.6 (DIN)
unnamed: ICL20.1 (R), MIN26.C
unnamed: ICL20.2 (G), MIN27.C
unnamed: ICL20.3 (B), MIN28.C
unnamed: ICL16.5 (DO), ICL19.6 (DIN)
unnamed: ICL23.1 (R), MIN29.C
unnamed: ICL23.2 (G), MIN30.C
unnamed: ICL23.3 (B), MIN31.C
unnamed: ICL19.5 (DO), ICL20.6 (DIN)
unnamed: ICL24.1 (R), MIN32.C
unnamed: ICL24.2 (G), MIN33.C
unnamed: ICL24.3 (B), MIN34.C
unnamed: ICL20.5 (DO), ICL23.6 (DIN)
unnamed: ICL27.1 (R), MIN35.C
unnamed: ICL27.2 (G), MIN36.C
unnamed: ICL27.3 (B), MIN37.C
unnamed: ICL23.5 (DO), ICL24.6 (DIN)
unnamed: ICL28.1 (R), MIN38.C
unnamed: ICL28.2 (G), MIN39.C
unnamed: ICL28.3 (B), MIN40.C
unnamed: ICL24.5 (DO), ICL27.6 (DIN)
unnamed: ICL31.1 (R), MIN41.C
unnamed: ICL31.2 (G), MIN42.C
unnamed: ICL31.3 (B), MIN43.C
unnamed: ICL27.5 (DO), ICL28.6 (DIN)
unnamed: ICL32.1 (R), MIN44.C
unnamed: ICL32.2 (G), MIN45.C
unnamed: ICL32.3 (B), MIN46.C
unnamed: ICL28.5 (DO), ICL31.6 (DIN)
unnamed: ICL35.1 (R), MIN47.C
unnamed: ICL35.2 (G), MIN48.C
unnamed: ICL35.3 (B), MIN49.C
unnamed: ICL31.5 (DO), ICL32.6 (DIN)
unnamed: ICL36.1 (R), MIN50.C
unnamed: ICL36.2 (G), MIN51.C
unnamed: ICL36.3 (B), MIN52.C
unnamed: ICL32.5 (DO), ICL35.6 (DIN)
unnamed: ICL39.1 (R), MIN53.C
unnamed: ICL39.2 (G), MIN54.C
unnamed: ICL39.3 (B), MIN55.C
unnamed: ICL35.5 (DO), ICL36.6 (DIN)
unnamed: ICL43.1 (R), MIN56.C
unnamed: ICL43.2 (G), MIN57.C
unnamed: ICL43.3 (B), MIN58.C
unnamed: ICL36.5 (DO), ICL39.6 (DIN)
unnamed: ICL39.5 (DO), ICL43.6 (DIN)
unnamed: DIN.1, ICH1.6 (DIN)
unnamed: HOUR11.C, ICC1.1 (R)
unnamed: HOUR0.C, ICC1.2 (G)
unnamed: HOUR1.C, ICC1.3 (B)
unnamed: DOUT.1, ICC4.5 (DO)
unnamed: HOUR2.C, ICC2.1 (R)
unnamed: HOUR3.C, ICC2.2 (G)
unnamed: HOUR4.C, ICC2.3 (B)
unnamed: HOUR5.C, ICC3.1 (R)
unnamed: HOUR6.C, ICC3.2 (G)
unnamed: HOUR7.C, ICC3.3 (B)
unnamed: HOUR8.C, ICC4.1 (R)
unnamed: HOUR9.C, ICC4.2 (G)
unnamed: HOUR10.C, ICC4.3 (B)
unnamed: ICC1.6 (DIN), ICL43.5 (DO)
unnamed: ICC1.5 (DO), ICC2.6 (DIN)
unnamed: ICC2.5 (DO), ICC3.6 (DIN)
unnamed: ICC3.5 (DO), ICC4.6 (DIN)
TOUCH: TOUCH.1, U$2.P$1, U$2.P$2

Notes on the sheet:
Touch

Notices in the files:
parts and their libraries:
SparkFun-Boards: Licensing: Creative Commons ShareAlike 4.0 International - https://creativecommons.org/licenses/by-sa/4.0
SparkFun2012: Licensing: CC v3.0 Share-Alike You are welcome to use this library for commercial purposes.
